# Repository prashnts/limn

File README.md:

## Limn: Pen Plotter with Toolchanger

I wanted to build a plotter that could draw in different colors without
manual color swaps. Limn is my attempt to build one using 3D printed and 3D
printer parts. It has a 5-slot toolchanger, auto tool offset calibration,
can plot on A6 and A5 (~90%) paper, and it runs on klipper.

Build logs are on [Hackaday.io](https://hackaday.io/project/205431-limn-pen-plotter-with-toolchanger),
and the printed parts can be found on [Printables](https://www.printables.com/model/1786450-limn-pen-plotter-with-automatic-tool-changer-parti).

Due to physical constraints and geometry, no two tools/pens will land at the same
point on paper for the given coordinate. This implies that they have each a
certain offset relative to an origin. If we assign a reference pen as the origin,
we can calibrate other tools by comparing the tip position (eg. by drawing and measuring).

This calibration can be done both by hand or automatically. There's an RFID tag
on each tool. Automatic offset calibration requires a sensing surface where the
tools can be probed. Limn can use a Resistive Touch Panel or an FSR matrix
to probe the tool's tips and estimate the XYZ offset with about <0.2mm (best: 0.04mm). 

Then I needed software to actually draw things. I first used PrusaSlicer with
an absurd hack: we can translate "retract", "unretract" as signals to move the
pen up or down... and it worked quite well!

There's an experimental "slicer" in `plot/` which will replace the slicer 
gcode generation. It parses the SVG files natively and handles images, gradient,
text well. It's also "vibecoded". It handles images and gradients with dithering
and the pens can be layered. I intend to refine it further, but it does the job
right now.

Lots of things are currently undocumented and unstable. It's a build log with
code, not a kit: expect to fork it and do some debugging. There's a
`CHANGELOG.md` containing the progress.

## What's where

- `klipper/`: Klipper configuration for the toolchanger motion and printer.
- `ext/limn/`: Klipper extension for complex tasks (eg. calibration).
- `plot/`: SVG to G-code ["Slicer"](plot/README.md).
- `limn_cam/`: (experimental) Z ladder, homographies, scan stitching.
- `micropython/`: firmware for the Dock and the bed MCUs.
- `slicer/`: the old PrusaSlicer based setup, retired.
- `GEOMETRY.md`: plotter coordinates, hardware.
- `docs/`: the details below.

## Development

Install Klipper and clone this repository in the home dir. Create following symlinks for plotter config and extension:

```sh
ln -sfn ~/limn/klipper ~/printer_data/config/limn
ln -sfn ~/limn/ext/limn ~/klipper/klippy/extras/limn
```

The extension requires some packages, so does the plot tool. Extension runs in
Klipper's venv and requires `numpy` to be installed. The plot tool needs `uv`.
In practice these config will require hand tuning for your specific device.

Then add the limn config files to your Klipper config:

```ini
[include limn/limn.cfg]
[include limn/leds.cfg]
[include limn/buzzer.cfg]
```

`printer.cfg` is not linked because Klipper's `SAVE_CONFIG` replaces it with a new one, which would break a symlink.

The plot UI runs next to Klipper (or preferably on a different computer). Its
workspace (the job, dropped SVGs, fonts) is `~/limn/plot-data`.

```sh
cd ~/limn && git pull && uv sync
sudo ln -sf ~/limn/limn_web.conf /etc/supervisor/conf.d/limn_web.conf
sudo supervisorctl reread && sudo supervisorctl update
sudo supervisorctl status limn_web      # then http://<pi>:4219
```

Note that there's no authentication yet, but Moonraker's auth will be supported soon.

A camera tool (wifi/wired) can be calibrated in the UI to scan the bed and plot 
over an existing image (not fully tested yet) or they may be stitched with hugin:

`sudo apt install hugin-tools enblend`

Camera scans are kept in RAM (`/dev/shm/limn-captures`, 2 GB at most).

- Run Tests: `uv run python ext/tests/test_*.py`
- Interact/Update MCUs: `uv run python micropython/mcu.py`
- Camera: `uv sync --extra cam`

## Calibrating the pens

A Bed containg a FSR matrix is used to calibrate XYZ offsets of the pens using
these commands:

```
LRT_CALIBRATE              ; with the reference pen in holder 45
LRT_PROBE_TOOL T=41   ; each other pen: its DX DY DZ go onto its tag
```

TODO: Description.
Everything about meshes, the sensor and its quirks is in `docs/calibration.md`.

## More notes

- `docs/calibration.md`: bed meshes, test marks, the FSR sensor and its survey.
- `docs/leds.md`: the LED matrix and dock strip, and what each state means.
- `docs/toolhead.md`: tool holders and tags, hand-docked tools, the toolhead's wiring, the endoscope.
- `docs/cameras.md`: adding a camera to the Scan tab and calibrating it.

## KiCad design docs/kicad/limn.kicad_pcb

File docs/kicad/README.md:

# Limn: the electronics in KiCad

A KiCad 9 project, `limn.kicad_pro`. The root sheet is the overview, with one sheet per role or board:

| Sheet | File | What's on it |
|---|---|---|
| Power | `power.kicad_sch` | The USB-C PD charger, the 12 V (motion, switched) and 9 V triggers. The bucks sit on their boards: LM_Buck0 by the Melzi, MP_Buck0 on the Aux PCB, MP_Buck1 on the hub board |
| Host (Pi 4) | `host.kicad_sch` | The Pi 4, its USB ports (the hub board on USB-A 3), a camera, I2C1 |
| Tool dock | `tool_dock.kicad_sch` | The MCP23017 and the 5 holder switches, the PN532 tag reader, the indockator strip |
| Melzi (motion) | `melzi.kicad_sch` | The Melzi, motors A/B, the X endstop, the EXT header, the OR gate (going), the plot bed's pull-up, LM_Buck0 (LM2596: +7V5_ZK, the motors only) |
| Toolhead | `toolhead.kicad_sch` | A2. The toolchanger as a PCB of its own (refs 50x, `toolhead_board.kicad_pcb`): the coupling (3 screws 5 V/GND/ID, 4 pogo pins D+/D-/GND/ID), the K lock's motor on 4 pogo pins, its key switch, the cell's pads (J501), 10 uF + 100 nF + an LED on +5V_TOOL, the FFC on an FPC-20P breakout (U506). The FFC (20P 0.5 mm, <= 15 cm) to a second breakout on the axis (U507, wired, no PCB): the USB-C cable to the hub board (W501, 5k1 on CC), CAT6 to LIT, the K ribbon to the Melzi. The axis: Z, the Y/Z endstops, the MPU9250, the endoscope, the BLTouch (gone). The FFC pinout and the tool classes in its notes |
| Aux MCU (rpi) | `aux.kicad_sch` | The Aux PCB, next version: a Waveshare RP2040-Zero (Klipper rpi) on the hub's DN4 (data only), MP_Buck0 (9 V to +5V_LED: the Zero, the LEDs, the buzzer), the buzzer, the MPU9250's I2C; the LEDs off the board |
| Calibration bed | `cal_bed.kicad_sch` | The bed's ID resistor, the FSR node (GP0 BED_DATA, GP2 BED_PROBE) and its 4 x 8 sheet with the row loads |
| Plot bed board | `plot_bed_board.kicad_sch` | The board of `limn.kicad_pcb` and what hangs off it (refs 95x, A2). Above: the two-strip cell (4 BF350s, one full bridge; its nets CELL_* on the head side), W951 = CAT6's bridge pairs to the board's rails (so E+/E- stay their own nets on the toolhead PCB), CAT6 through the chain (orange = E, blue = S, white-green = the tool's ID, green = its GND return on J952.6; the browns spare) to the board at the back: one ADS1220, the touch line (Q951, Q952 in series for BED_PROBE), the tool's ID line, LEDs, J957 to the hub board (the hub's DN3: 5 V on RAW, D+/D- on the Pro Micro's pads underneath; GP9 = `TOOL_5V_EN` back; +5V_TOOL_IN for the bed). Below: the bed dock's work, DETECT (GP29), BED_DATA (GP0, half-duplex), BED_PROBE (GP1), two Pololu Mini MOSFET Slide Switches on MP_Buck1 (+5V_TOOL_IN): U956 on GP4 = the bed (BED_PWR, F952), U957 on GP5 = +5V_SW on J959 (the LEDs, spare), J958, and the dock's pogo J701. Its board headers are 1x1s (J952.1, J957.4, ...), one per pin, to place each where its wiring wants |
| Hub board (USB + tool 5 V) | `hub.kicad_sch` | The FE1.1s hub on its own cable from the Pi (Adafruit USB-C breakout; the Pi powers the hub): DN1 the Melzi, DN2 the tool, DN4 the Aux MCU: data only; DN3 the plot bed board, with the hub's 5 V. The tool's 5 V: 9 V in, MP_Buck1, the Pololu switch, a polyfuse, the tool's USB-C cable on a second Adafruit breakout (U1007: +5V_TOOL, DN2) |
| Beam bed (XY) | `beam_bed.kicad_sch` | A detachable bed (refs 85x), its own PCB (`beam_bed_board.kicad_pcb`): a Waveshare RP2040-Tiny, two 940 nm IR LEDs (AO3400, 100R, pulsed from BED_PWR) and two PT1206BS (10k emitter loads into GP26/27) in an L of 15 mm slots; GP0 = BED_DATA (half-duplex UART, one wire), GP1 = BED_PROBE (the trigger, high = OK), DETECT = the ID resistor only. 0805 resistors. Z from the head's load cell |

How to read it:
- **Sheets meet through global labels** (`USB_*`, `I2C1_*`, `MOT_*`, `ENDSTOP_*`, `PROBE_*`, `BED_*`, ...) and **named power rails** (`+12V`, `+7V5_ZK`, `+9V`, `+5V_LED`, `+5V_TOOL`, `+5V_TOOL_IN`, `+5V_HUB`, `+5V_MELZI`, `+3V3_PI`, `+3V3_AUX`, `+3V3_PB`, `+3V3_PH`). All GND is one net.
- **Solid boxes**: one board or assembly. **Dashed boxes**: planned, or going; their parts are DNP.
- **Boards are blocks** with the pins Limn uses, named as the code names them. The Pro Micro is drawn with its full header in physical order. A USB link is one pin (the cable).
- **References per sheet**: power 1xx, host 2xx, tool dock 3xx, Melzi 4xx, toolhead 5xx, Aux 6xx, the dock's pogo 7xx (J701), calibration bed 8xx (the beam bed 85x), plot bed board 95x, hub board 10xx.
- **Set aside** (2026-10-23, not drawn): the bed on three load-cell feet (the old *Plot bed* sheet, refs 90x), the RTP node, a toolhead MCU, the QRE1113 on the toolhead (U954, R961, C957, GP28). Their drawing code is in `kicad_gen/aside.py`, to bring one back as it was.
- Wires turn at 45°.

Gathered from the code and the docs on 2026-10-16: `notebooks/pinout.md`, `micropython/nodes/*.json`, `klipper/*.cfg`, `projects/limn/content/electronics.md`, `docs/block-diagrams.md`, `docs/load-cell.md`, `TODO.md`.

## Regenerating

```
python3 docs/kicad/gen.py --force --check
```

`kicad_gen/` holds the drawing code: `core.py` (the writer, wires, labels, enclosures), `boards.py` (the blocks), `sheets_a.py` / `sheets_b.py` (one function per sheet), `aside.py` (what is set aside). `gen.py` keeps KiCad's settings in `limn.kicad_pro` and only rewrites its sheet list. `--check` runs ERC, `audit.py` (a net joining two signal pins of one part: the shorts ERC can't see between passive pins) and writes one SVG per sheet into `svg/`. Today (2026-10-23): ERC 0 errors 0 warnings, audit ok. R958 fitted (as traced on the PCB), TOUCH_GP on GP2 only.

Footprints: *Plot bed board* has them (perfboard: R and C in 0805 since 2026-10-23, the fuse in 1812; the modules in `limn.pretty`, written by `kicad_gen/footprints.py`, listed in `fp-lib-table`), and so do the three boards of their own below. The other sheets don't yet.

**One PCB per board.** `limn.kicad_pcb` is the plot bed board's (Update PCB from Schematic, F8). Its perfboard's copper is drawn on Dwgs.User between the hole dots (`perfboard.strips`, 2026-10-23): the top and bottom rows one strip each, the 15 rows between joined down each column in 5 groups of 3. The hub board, the Aux PCB and the beam bed are boards of their own; their parts are "not on board" in the schematic (`sheets_b.own_board`), so F8 never puts them on `limn.kicad_pcb`. Their boards are made from the netlist by `tools/mkboard.py hub|aux|beam|head`: the sheet's parts with a footprint, their nets, a first placement (not routed). It never writes over an existing board (`--force` does); open them in the PCB editor on their own (no project of their own, so no F8: a schematic change goes in by hand or a sync like `tools/sync.py`).

| Board | File | What |
|---|---|---|
| Hub board | `hub_board.kicad_pcb` | Perfboard 38 x 17 holes (as the plot bed board's; its strips not drawn yet). The FE1.1s and the USB-C breakout's pad maps are placeholders: map the real boards before soldering |
| Aux PCB | `aux_board.kicad_pcb` | Perfboard 38 x 17. MP_Buck0 drawn as the same mini buck as MP_Buck1; the LEDs (U602/U603) off the board |
| Toolhead PCB | `toolhead_board.kicad_pcb` | Its own project (`toolhead_board.kicad_pro`): the Toolhead sheet drawn again as `toolhead_board.kicad_sch` (gen.py `STANDALONE`), so the board and the schematic link (F8, cross-probing); its global labels dangle there (their other ends are in `limn.kicad_pro`). Edit the generator, not one copy. A PCB, 61 x 50.8 mm for now (a first outline: shape it to the head). The FPC-20P breakout (`limn:FPC20_breakout`, from its photo; its STEP to come), SMD pogo pins D 2.0 x 5 (`limn:Pogo_pin_D2.0_L5.0`), the K motor with its flex on 4 pogos (`limn:Stepper_slider_5mm_flex4`), the key switch (`limn:Micro_limit_sw_inline`), M3 pad holes for the screws, the cell's wires (SolderWire 1x04), 0805. STEPs from the user's models in `limn.3dshapes/` |
| Beam bed | `beam_bed_board.kicad_pcb` | A PCB, 43.2 x 33.0 mm, 1.6 mm (thinner for the bed: set it in Board Setup). 0805, the LEDs/PTs in 1206 (where they go depends on the slots), the pogo as a 1x05 2.54 mm row |

The RP2040-Zero and RP2040-Tiny (same 23 castellated holes, rows 15.24 mm apart) use Waveshare's pin numbers (GP0-15 = 1-16, GP26-29 = 17-20, 3V3 21, GND 22, 5V 23; 24 = the USB), with Waveshare's STEP models in `limn.3dshapes/` (gzipped, `.stpZ`). The library footprints point at KiCad's 3D models (`${KICAD9_3DMODEL_DIR}`): install `kicad-packages3d` to see them.

Once the schematic is edited in KiCad, regenerating overwrites the edits: don't, or move the change into the generator first.

## To fill in

- [ ] The FE1.1s breakout (which board) and its pad map: `limn:FE1.1s_USB_hub_breakout` is a placeholder (U1002).
- [ ] The Adafruit USB-C breakout's pin order (U1001: VBUS, D+, D-, GND in a row for now).
- [ ] The beam bed's pogo: its pitch and pin order (J851: a 1x05 2.54 mm row for now); where the LEDs/PTs sit against the slots; the board's thickness.
- [ ] The toolhead PCB: the K flex pads' pitch and place (3.0 mm past the motor's end, a placeholder), the key switch's tabs (from the model), the screws' size and places, the outline; the breakout's STEP (the user, 2026-10-30).
- [x] The FFC: 1 -> 1 (the cell reads right through pins 2-5, 2026-11-01; reversed they'd land on 16-19). Meter 13-15 before power anyway.
- [ ] The bed pogo connector's pin order (power, GND, DETECT, TX, RX).
- [ ] The cameras on the Pi: which is on which port, and which devices are on the hub vs straight on the Pi today.
- [ ] The buzzer circuit: gate resistor, supply, flyback diode.
- [ ] The Pico's VSYS (USB only, or the Aux PCB's LM2596 through a diode?), and where the MPU9250 gets its VCC.
- [ ] The MCP23017 breakout's RST pin.
- [x] The ADS1220 module's header order: from the photo (2026-10-18), DIP numbering, top view; footprint `limn:ADS1220_module`.
- [ ] The Pololu Mini MOSFET Slide Switch's pad map (U1006 on the hub board).
- [ ] Where the Pro Micro's D+/D- pads are underneath (footprint pads 30/31 are placeholders by the USB-C).
- [ ] `klipper/leds.cfg` for the RP2040-Zero (lamp gpio16 → 14, indockator gpio17 → 13) and the merged Dock/plot bed firmware (dock pins GP29, GP0/1, GP4 = BED_EN, GP5 = SW_5V_EN, high = on; CS2 on GP21, LED_R/LED_G gone).
- [ ] The FSR board's series resistors on the rows (values).
- [ ] The Melzi's endstop headers (2 or 3 pins), and whether the BLTouch and the OR gate are already out.

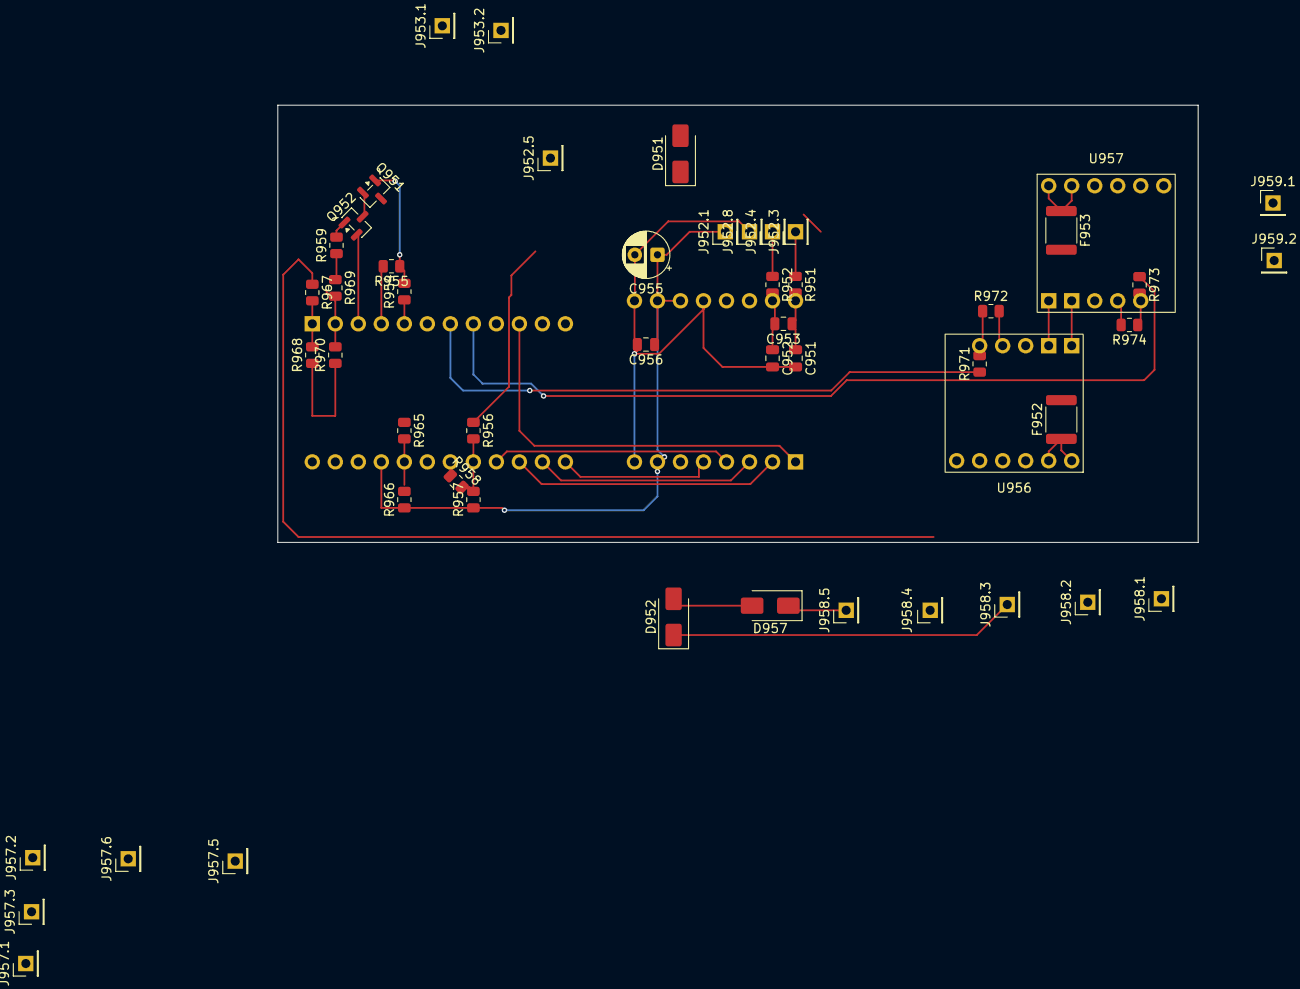
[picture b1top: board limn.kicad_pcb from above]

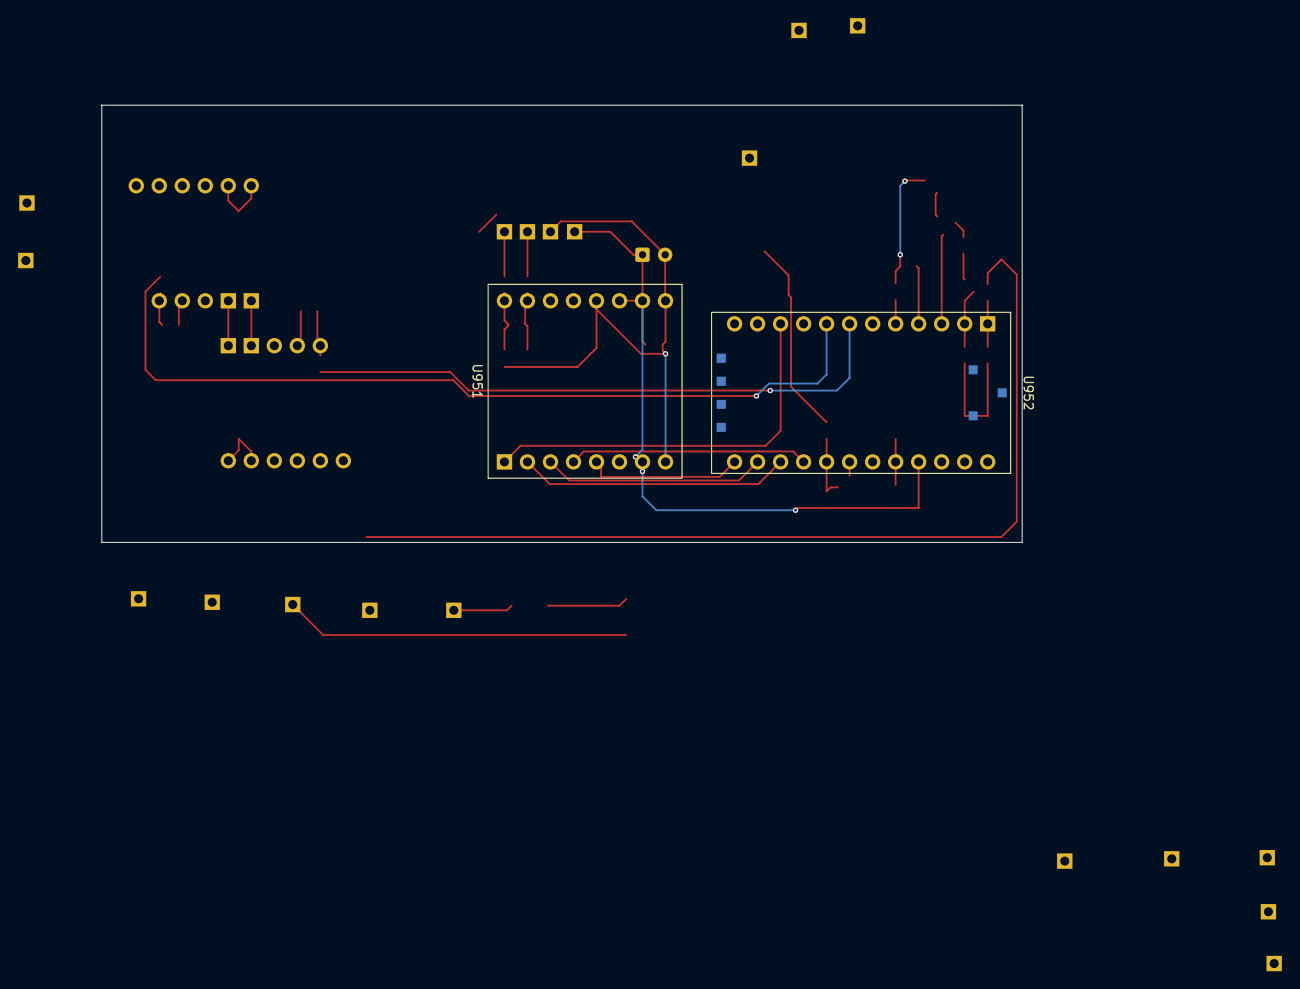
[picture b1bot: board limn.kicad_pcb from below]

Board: 2 copper layers, 101.6 x 48.3 mm, 53 parts (2 on the bottom side), 37 nets.

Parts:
C951, C952: 4n7 C0G; C_0805_2012Metric
C953: 47n; C_0805_2012Metric
C955: 47u; CP_Radial_D5.0mm_P2.50mm
C956: 100n; C_0805_2012Metric
D951, D952, D957: SMAJ3.3A; D_SMA
F952, F953: PPTC 1812 1A 6V; Fuse_1812_4532Metric
J952.1: CAT6 1; PinHeader_1x01_P2.54mm_Vertical
J952.3: CAT6 3; PinHeader_1x01_P2.54mm_Vertical
J952.4: CAT6 4; PinHeader_1x01_P2.54mm_Vertical
J952.5: CAT6 5; PinHeader_1x01_P2.54mm_Vertical
J952.8: CAT6 8; PinHeader_1x01_P2.54mm_Vertical
J953.1: to the Melzi (EXT A4) 1; PinHeader_1x01_P2.54mm_Vertical
J953.2: to the Melzi (EXT A4) 2; PinHeader_1x01_P2.54mm_Vertical
J957.1: to the hub board (J1002) 1; PinHeader_1x01_P2.54mm_Vertical
J957.2: to the hub board (J1002) 2; PinHeader_1x01_P2.54mm_Vertical
J957.3: to the hub board (J1002) 3; PinHeader_1x01_P2.54mm_Vertical
J957.5: to the hub board (J1002) 5; PinHeader_1x01_P2.54mm_Vertical
J957.6: to the hub board (J1002) 6; PinHeader_1x01_P2.54mm_Vertical
J958.1: to the bed dock (pogo) 1; PinHeader_1x01_P2.54mm_Vertical
J958.2: to the bed dock (pogo) 2; PinHeader_1x01_P2.54mm_Vertical
J958.3: to the bed dock (pogo) 3; PinHeader_1x01_P2.54mm_Vertical
J958.4: to the bed dock (pogo) 4; PinHeader_1x01_P2.54mm_Vertical
J958.5: to the bed dock (pogo) 5; PinHeader_1x01_P2.54mm_Vertical
J959.1: +5V Toolchanger USB 1; PinHeader_1x01_P2.54mm_Vertical
J959.2: +5V Toolchanger USB 2; PinHeader_1x01_P2.54mm_Vertical
Q951: MMBT3904 / BC847 (SOT-23); SOT-23
Q952: AO3400; SOT-23
R951, R952, R958, R959, R971, R973: 1k; R_0805_2012Metric
R954, R968: 4k7; R_0805_2012Metric
R955, R972, R974: 100k; R_0805_2012Metric
R956, R965, R967, R969: 100R; R_0805_2012Metric
R957, R966, R970: 10k; R_0805_2012Metric
U951: ADS1220 module (the sum chip); ADS1220_module
U952: SparkFun Pro Micro RP2040 (top view, USB-C up); SparkFun_Pro_Micro_RP2040
U956, U957: Pololu mini slide sw. #2810; Pololu_Mini_MOSFET_Slide_Switch

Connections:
+3V3_PH: C955.1, C956.1, J952.1.1, R957.1, R966.1, R968.1, R970.1, U951.7 (DVDD), U951.10 (AVDD), U951.11 (REFP0), U952.16 (3V3)
+5V_HUB: J957.1.1, U952.13 (RAW)
+5V_SW: F953.2, J959.1.1
+5V_TOOL_IN: J957.5.1, U956.1 (VIN), U957.1 (VIN)
/Plot bed board/AIN_N: C952.1, C953.2, R952.2, U951.15 (AIN1)
/Plot bed board/AIN_P: C951.1, C953.1, R951.2, U951.16 (AIN0)
/Plot bed board/CIPO: U951.2 (MISO), U952.22 (GP20/CIPO)
/Plot bed board/COPI: U951.3 (MOSI), U952.23 (GP23/COPI)
/Plot bed board/CS2: U951.5 (CS), U952.24 (GP21/CS)
/Plot bed board/DRDY2: U951.1 (DRDY), U952.10 (GP7)
/Plot bed board/ID_PU: R958.1, U952.19 (GP27/A1)
/Plot bed board/SCK: U951.4 (SCLK), U952.21 (GP22/SCK)
/Plot bed board/SIG_N: J952.4.1, R952.1
/Plot bed board/SIG_P: J952.3.1, R951.1
/Plot bed board/TOOL_ID_IN: R956.2, R957.2, R958.2, U952.20 (GP26/A0)
/Plot bed board/TOUCH_GP: R954.1, U952.5 (GP2)
BED_DATA: J958.4.1, R967.1
BED_DETECT: D952.1 (A1), J958.3.1, R965.1
BED_DET_IN: R965.2, R966.2, U952.17 (GP29/A3)
BED_EN: R971.1, U952.7 (GP4)
BED_IO: R967.2, R968.2, U952.1 (GP0/TX)
BED_PROBE: D957.1 (A1), J958.5.1, R959.1, R969.1
BED_PROBE_IN: R969.2, R970.2, U952.2 (GP1/RX)
BED_PWR: F952.2, J958.1.1
GND: C951.2, C952.2, C955.2, C956.2, D951.2 (A2), D952.2 (A2), D957.2 (A2), J952.8.1, J953.2.1, J957.6.1, J958.2.1, J959.2.1, Q952.2 (S), R955.2, R972.2, R974.2, U951.8 (DGND), U951.9 (AGND), U951.12 (REFN0), U952.3 (GND), U952.4 (GND), U952.14 (GND), U956.3 (GND), U957.3 (GND)
unnamed: Q951.1 (B), R954.2, R955.1
unnamed: Q951.2 (E), Q952.3 (D)
unnamed: Q952.1 (G), R959.2
unnamed: R971.2, R972.1, U956.2 (ON)
unnamed: F952.1, U956.4 (VOUT)
unnamed: R973.2, R974.1, U957.2 (ON)
unnamed: F953.1, U957.4 (VOUT)
PM_USB_DN: J957.3.1, U952.31 (D-)
PM_USB_DP: J957.2.1, U952.30 (D+)
PROBE_A4: J953.1.1, Q951.3 (C)
SW_5V_EN: R973.1, U952.8 (GP5)
TOOL_ID: D951.1 (A1), J952.5.1, R956.1

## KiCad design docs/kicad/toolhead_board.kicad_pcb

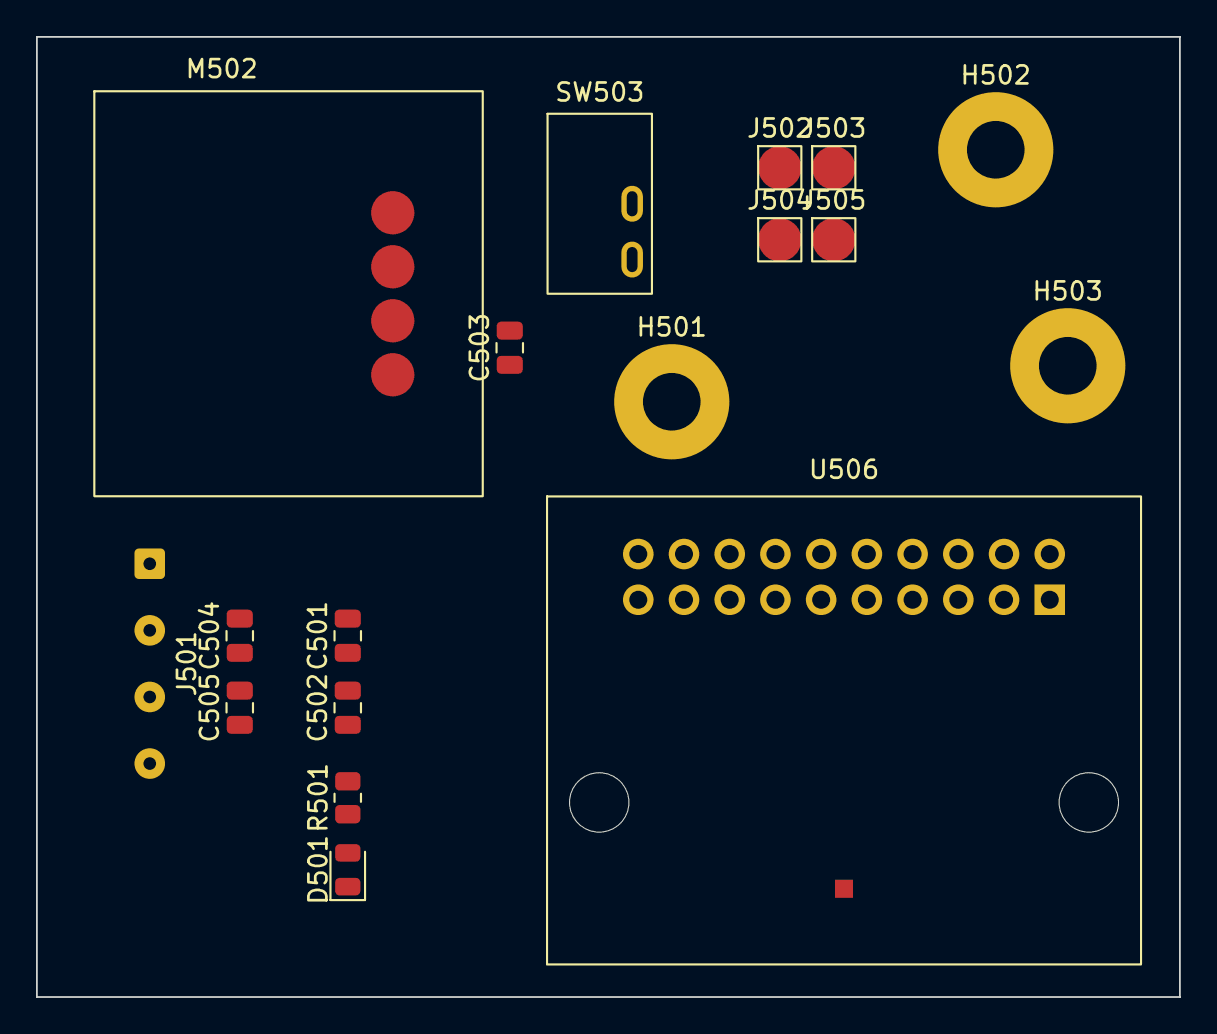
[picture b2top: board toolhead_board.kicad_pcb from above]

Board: 2 copper layers, 63.5 x 53.3 mm, 18 parts (0 on the bottom side), 15 nets, no tracks yet.

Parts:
C501: 10u; C_0805_2012Metric
C502, C505: 100n; C_0805_2012Metric
C503: 10n; C_0805_2012Metric
C504: 10n C0G; C_0805_2012Metric
D501: LED yellow; LED_0805_2012Metric
H501: screw right, 5V; MountingHole_3.2mm_M3_Pad
H502: screw left, GND; MountingHole_3.2mm_M3_Pad
H503: screw top, ID; MountingHole_3.2mm_M3_Pad
J501: cell pads; SolderWire-0.127sqmm_1x04_P3.7mm_D0.48mm_OD1mm
J502, J503, J504, J505: pogo; Pogo_pin_D2.0_L5.0
M502: 10 mm linear micro stepper (K, the key lock); Stepper_slider_5mm_flex4
R501: 4k7; R_0805_2012Metric
SW503: key switch (K); Micro_limit_sw_inline
U506: FPC-20P breakout (head); FPC20_breakout

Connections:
+5V_TOOL: C501.1, C502.1, H501.1, R501.1, U506.13, U506.14, U506.15
CELL_EXC_N: C505.2, J501.4, U506.5
CELL_EXC_P: C505.1, J501.1, U506.2
CELL_SIG_N: C504.2, J501.3, U506.4
CELL_SIG_P: C504.1, J501.2, U506.3
ENDSTOP_K: C503.1, SW503.1, U506.7
GND: C501.2, C502.2, C503.2, D501.1, H502.1, J504.1, SW503.2, U506.1, U506.6, U506.8, U506.11, U506.16
MOT_K_1A: M502.1, U506.17
MOT_K_1B: M502.2, U506.18
MOT_K_2A: M502.3, U506.19
MOT_K_2B: M502.4, U506.20
unnamed: D501.2, R501.2
TOOL_ID: H503.1, J505.1, U506.12
TOOL_USB_DN: J503.1, U506.10
TOOL_USB_DP: J502.1, U506.9

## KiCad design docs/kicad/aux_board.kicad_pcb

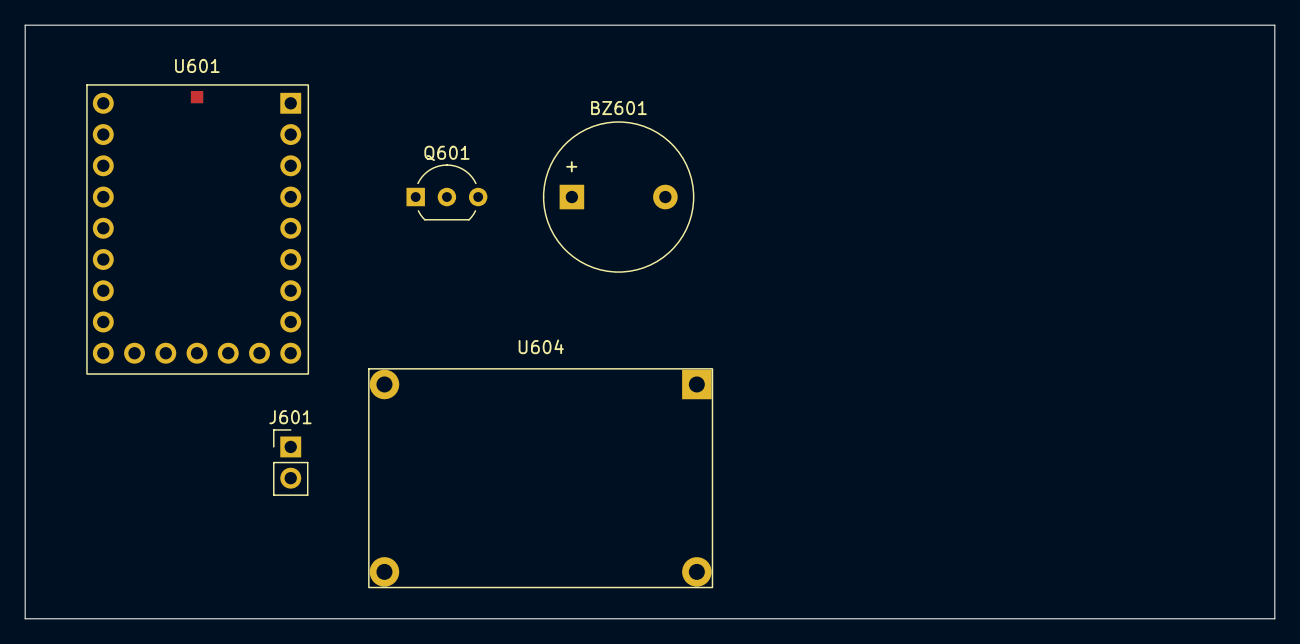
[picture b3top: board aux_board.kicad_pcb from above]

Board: 2 copper layers, 101.6 x 48.3 mm, 5 parts (0 on the bottom side), 5 nets, no tracks yet.

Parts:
BZ601: buzzer; Buzzer_12x9.5RM7.6
J601: 9 V in (Trigger1); PinHeader_1x02_P2.54mm_Vertical
Q601: 2N7000; TO-92_Inline_Wide
U601: RP2040-Zero (rpi); Waveshare_RP2040_Zero
U604: MP1495 5 V (MP_Buck0); Mini_buck_3A

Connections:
+5V_LED: BZ601.1, U601.23, U604.3
+9V: J601.1, U604.1
GND: J601.2, Q601.1, U601.22, U604.2, U604.4
unnamed: BZ601.2, Q601.3
unnamed: Q601.2, U601.10

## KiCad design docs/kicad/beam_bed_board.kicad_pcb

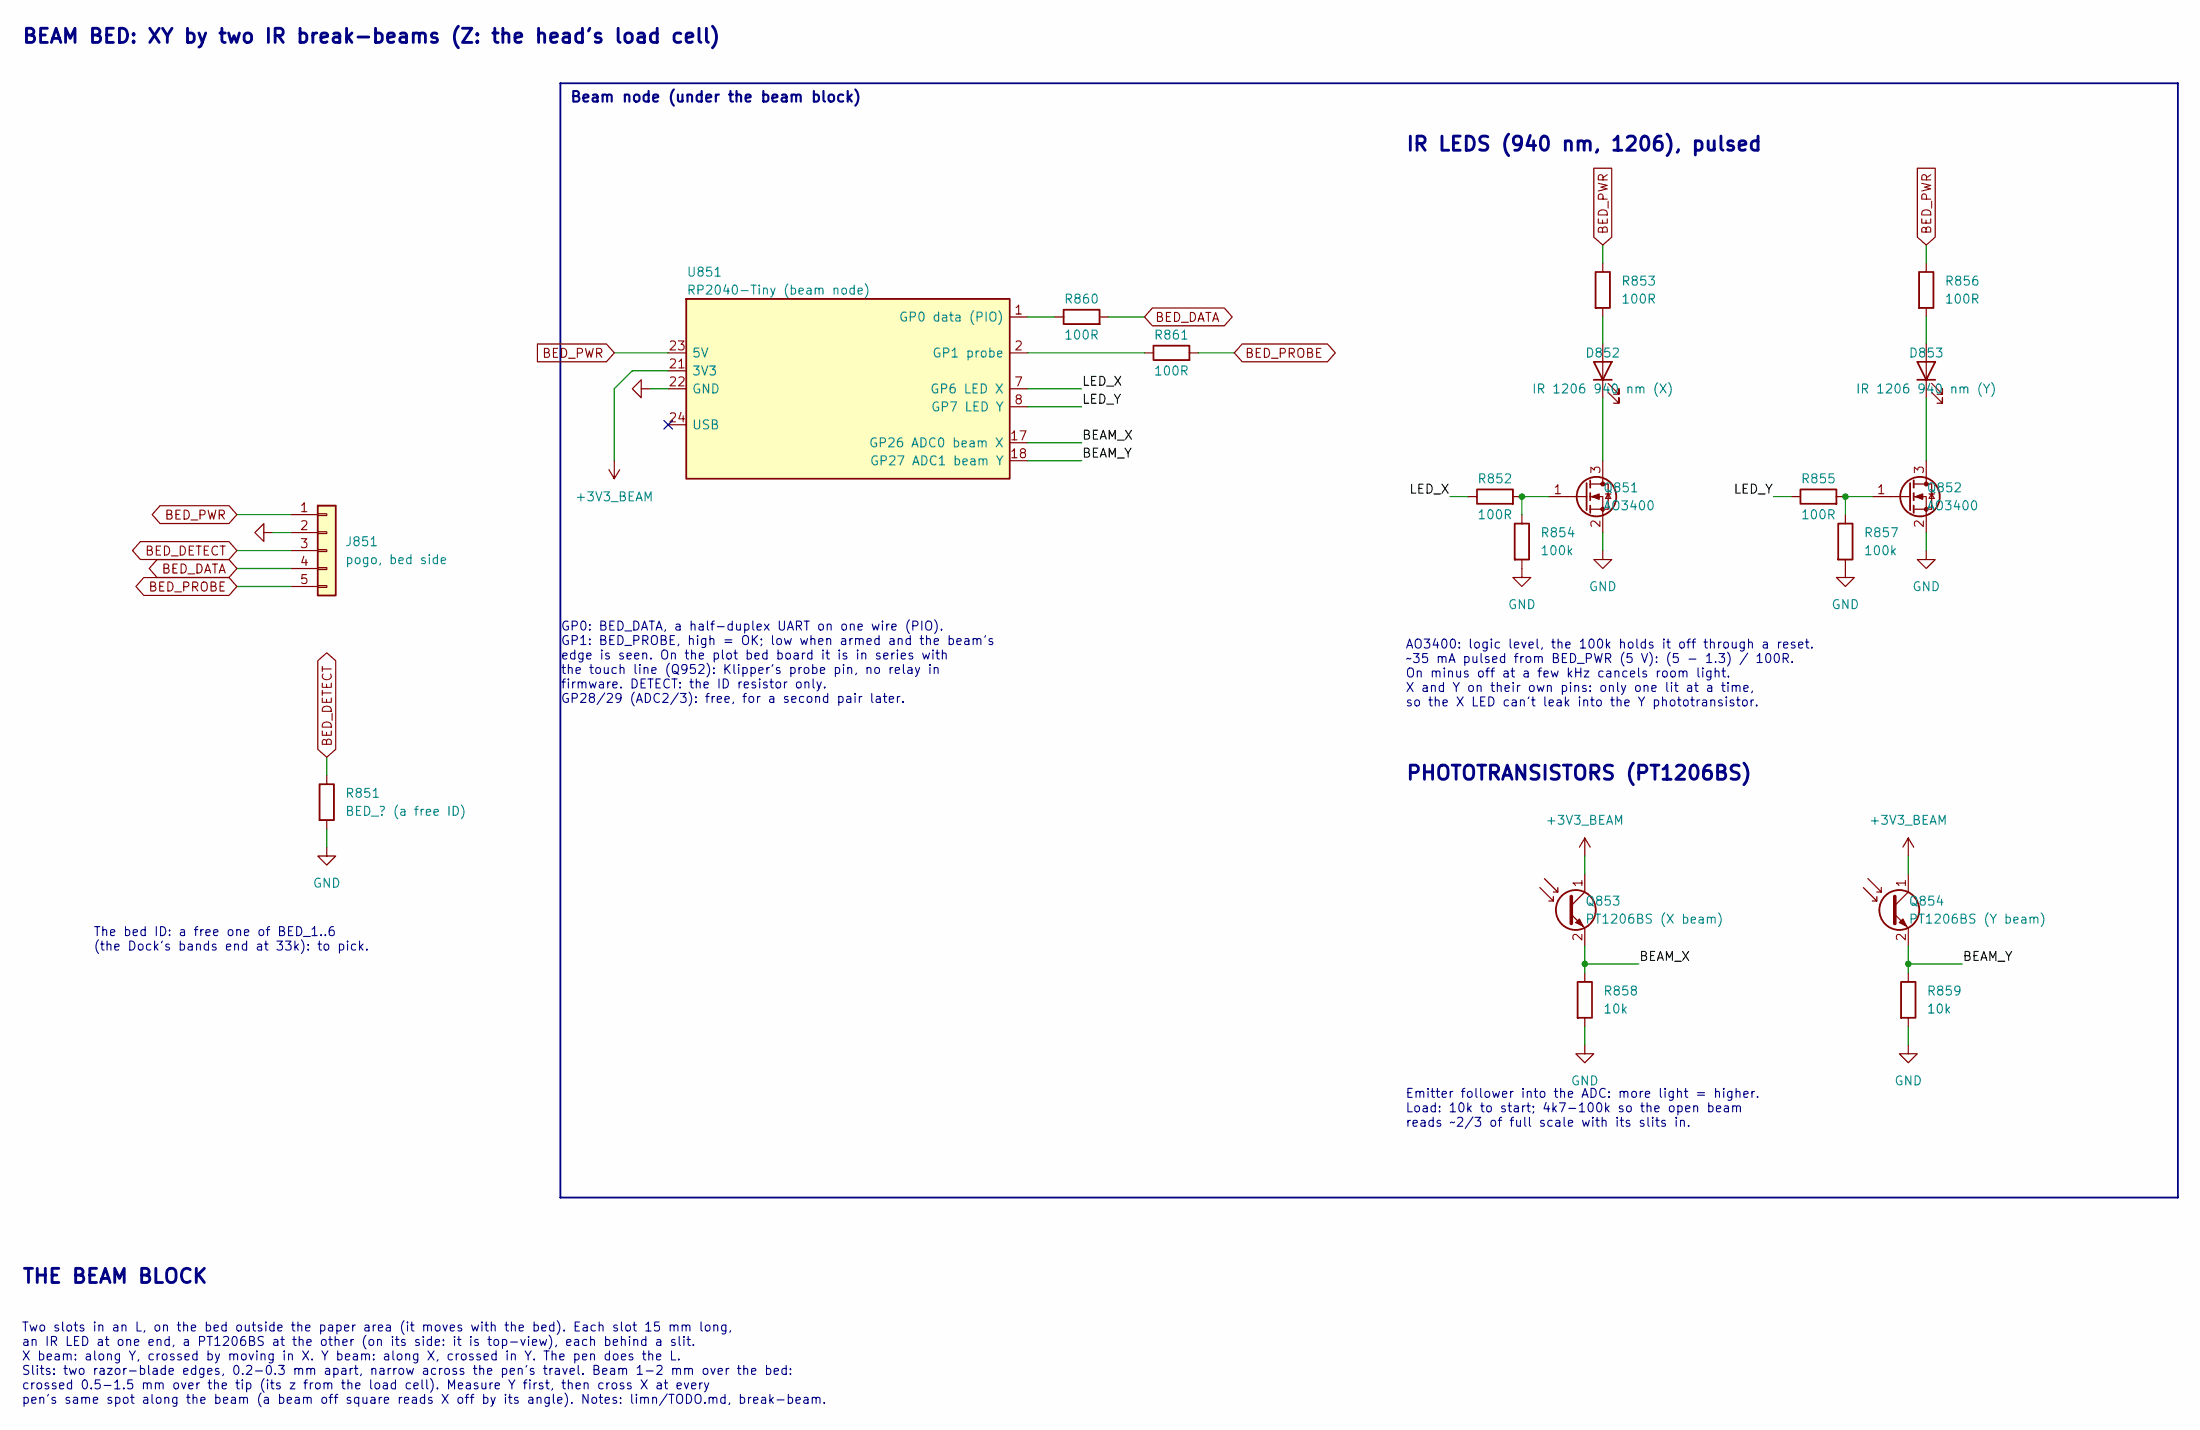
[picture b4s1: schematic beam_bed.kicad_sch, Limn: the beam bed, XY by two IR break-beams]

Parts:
D852: IR 1206 940 nm (X); LED_1206_3216Metric
D853: IR 1206 940 nm (Y); LED_1206_3216Metric
J851: pogo, bed side; PinHeader_1x05_P2.54mm_Vertical
Q851, Q852: AO3400; SOT-23
Q853: PT1206BS (X beam); LED_1206_3216Metric
Q854: PT1206BS (Y beam); LED_1206_3216Metric
R851: BED_? (a free ID); R_0805_2012Metric
R852, R853, R855, R856, R860, R861: 100R; R_0805_2012Metric
R854, R857: 100k; R_0805_2012Metric
R858, R859: 10k; R_0805_2012Metric
U851: RP2040-Tiny (beam node); Waveshare_RP2040_Tiny

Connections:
+3V3_BEAM: Q853.1 (C), Q854.1 (C), U851.21 (3V3)
/Beam bed (XY)/BEAM_X: Q853.2 (E), R858.1, U851.17 (GP26 ADC0 beam X)
/Beam bed (XY)/BEAM_Y: Q854.2 (E), R859.1, U851.18 (GP27 ADC1 beam Y)
/Beam bed (XY)/LED_X: R852.1, U851.7 (GP6 LED X)
/Beam bed (XY)/LED_Y: R855.1, U851.8 (GP7 LED Y)
BED_DATA: J851.4, R860.2
BED_DETECT: J851.3, R851.1
BED_PROBE: J851.5, R861.2
BED_PWR: J851.1, R853.1, R856.1, U851.23 (5V)
GND: J851.2, Q851.2 (S), Q852.2 (S), R851.2, R854.2, R857.2, R858.2, R859.2, U851.22 (GND)
unnamed: D852.2 (A), R853.2
unnamed: D852.1 (K), Q851.3 (D)
unnamed: D853.2 (A), R856.2
unnamed: D853.1 (K), Q852.3 (D)
unnamed: Q851.1 (G), R852.2, R854.1
unnamed: Q852.1 (G), R855.2, R857.1
unnamed: R860.1, U851.1 (GP0 data (PIO))
unnamed: R861.1, U851.2 (GP1 probe)

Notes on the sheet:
BEAM BED: XY by two IR break-beams (Z: the head's load cell)
The bed ID: a free one of BED_1..6 (the Dock's bands end at 33k): to pick.
GP0: BED_DATA, a half-duplex UART on one wire (PIO). GP1: BED_PROBE, high = OK; low when armed and the beam's edge is seen. On the plot bed board it is in series with the touch line (Q952): Klipper's probe pin, no relay in firmware. DETECT: the ID resistor only. GP28/29 (ADC2/3): free, for a second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
IR LEDS (940 nm, 1206), pulsed
AO3400: logic level, the 100k holds it off through a reset. ~35 mA pulsed from BED_PWR (5 V): (5 - 1.3) / 100R. On minus off at a few kHz cancels room light. X and Y on their own pins: only one lit at a time, so the X LED can't leak into the Y phototransistor.
PHOTOTRANSISTORS (PT1206BS)
Emitter follower into the ADC: more light = higher. Load: 10k to start; 4k7-100k so the open beam reads ~2/3 of full scale with its slits in.
Beam node (under the beam block)
THE BEAM BLOCK
Two slots in an L, on the bed outside the paper area (it moves with the bed). Each slot 15 mm long, an IR LED at one end, a PT1206BS at the other (on its side: it is top-view), each behind a slit. X beam: along Y, crossed by moving in X. Y beam: along X, crossed in Y. The pen does the L. Slits: two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

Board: 2 copper layers, 19 parts (0 on the bottom side), 18 nets, no tracks yet.

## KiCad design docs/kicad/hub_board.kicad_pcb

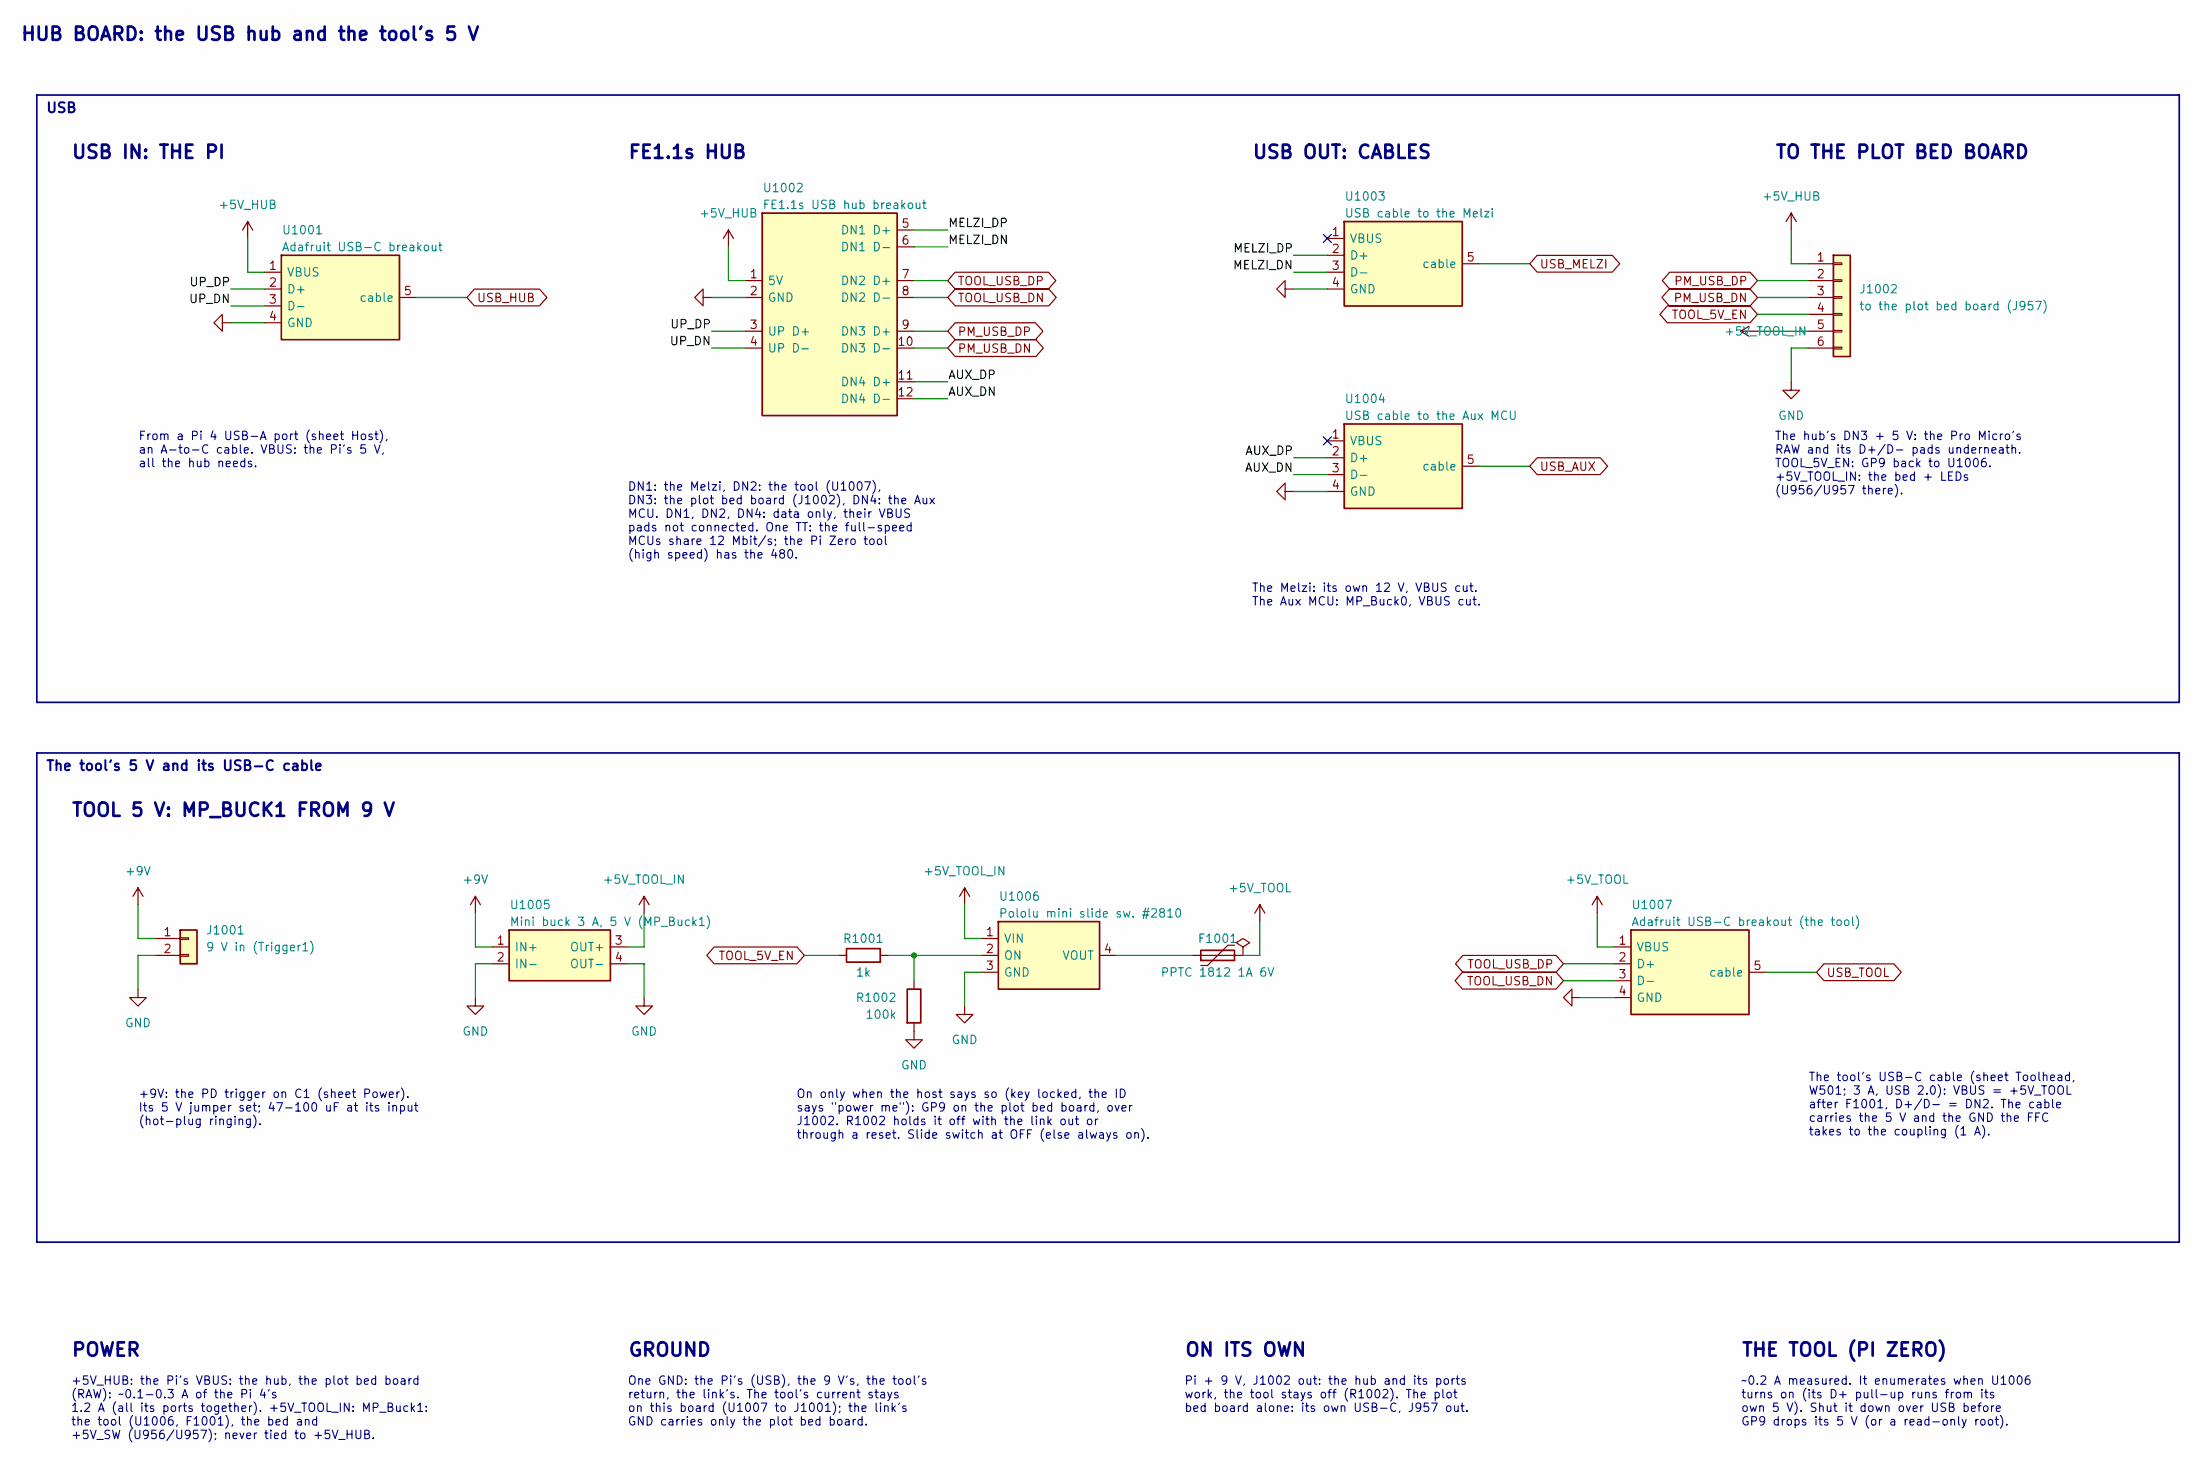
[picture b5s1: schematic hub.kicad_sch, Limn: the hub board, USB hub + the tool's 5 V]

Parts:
F1001: PPTC 1812 1A 6V; Fuse_1812_4532Metric
J1001: 9 V in (Trigger1); PinHeader_1x02_P2.54mm_Vertical
J1002: to the plot bed board (J957); PinHeader_1x06_P2.54mm_Vertical
R1001: 1k; R_0805_2012Metric
R1002: 100k; R_0805_2012Metric
U1001: Adafruit USB-C breakout; Adafruit_USB_C_breakout
U1002: FE1.1s USB hub breakout; FE1.1s_USB_hub_breakout
U1003: USB cable to the Melzi; USB_cable_pads
U1004: USB cable to the Aux MCU; USB_cable_pads
U1005: Mini buck 3 A, 5 V (MP_Buck1); Mini_buck_3A
U1006: Pololu mini slide sw. #2810; Pololu_Mini_MOSFET_Slide_Switch
U1007: Adafruit USB-C breakout (the tool); Adafruit_USB_C_breakout

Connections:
+5V_HUB: J1002.1, U1001.1 (VBUS), U1002.1 (5V)
+5V_TOOL: F1001.2, U1007.1 (VBUS); also elsewhere on the board
+5V_TOOL_IN: J1002.5, U1005.3 (OUT+), U1006.1 (VIN)
+9V: J1001.1, U1005.1 (IN+)
/Hub board (USB + tool 5 V)/AUX_DN: U1002.12 (DN4 D-), U1004.3 (D-)
/Hub board (USB + tool 5 V)/AUX_DP: U1002.11 (DN4 D+), U1004.2 (D+)
/Hub board (USB + tool 5 V)/MELZI_DN: U1002.6 (DN1 D-), U1003.3 (D-)
/Hub board (USB + tool 5 V)/MELZI_DP: U1002.5 (DN1 D+), U1003.2 (D+)
/Hub board (USB + tool 5 V)/UP_DN: U1001.3 (D-), U1002.4 (UP D-)
/Hub board (USB + tool 5 V)/UP_DP: U1001.2 (D+), U1002.3 (UP D+)
GND: J1001.2, J1002.6, R1002.2, U1001.4 (GND), U1002.2 (GND), U1003.4 (GND), U1004.4 (GND), U1005.2 (IN-), U1005.4 (OUT-), U1006.3 (GND), U1007.4 (GND); also elsewhere on the board
unnamed: R1001.2, R1002.1, U1006.2 (ON)
unnamed: F1001.1, U1006.4 (VOUT)
PM_USB_DN: J1002.3, U1002.10 (DN3 D-)
PM_USB_DP: J1002.2, U1002.9 (DN3 D+)
TOOL_5V_EN: J1002.4, R1001.1
TOOL_USB_DN: U1002.8 (DN2 D-), U1007.3 (D-); also elsewhere on the board
TOOL_USB_DP: U1002.7 (DN2 D+), U1007.2 (D+); also elsewhere on the board
USB_AUX: U1004.5 (cable)
USB_HUB: U1001.5 (cable)
USB_MELZI: U1003.5 (cable)

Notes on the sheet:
HUB BOARD: the USB hub and the tool's 5 V
USB IN: THE PI
From a Pi 4 USB-A port (sheet Host), an A-to-C cable. VBUS: the Pi's 5 V, all the hub needs.
FE1.1s HUB
DN1: the Melzi, DN2: the tool (U1007), DN3: the plot bed board (J1002), DN4: the Aux MCU. DN1, DN2, DN4: data only, their VBUS pads not connected. One TT: the full-speed MCUs share 12 Mbit/s; the Pi Zero tool (high speed) has the 480.
USB OUT: CABLES
The Melzi: its own 12 V, VBUS cut. The Aux MCU: MP_Buck0, VBUS cut.
TO THE PLOT BED BOARD
The hub's DN3 + 5 V: the Pro Micro's RAW and its D+/D- pads underneath. TOOL_5V_EN: GP9 back to U1006. +5V_TOOL_IN: the bed + LEDs (U956/U957 there).
USB
TOOL 5 V: MP_BUCK1 FROM 9 V
+9V: the PD trigger on C1 (sheet Power). Its 5 V jumper set; 47-100 uF at its input (hot-plug ringing).
On only when the host says so (key locked, the ID says "power me"): GP9 on the plot bed board, over J1002. R1002 holds it off with the link out or through a reset. Slide switch at OFF (else always on).
The tool's USB-C cable (sheet Toolhead, W501; 3 A, USB 2.0): VBUS = +5V_TOOL after F1001, D+/D- = DN2. The cable carries the 5 V and the GND the FFC takes to the coupling (1 A).
The tool's 5 V and its USB-C cable
POWER
+5V_HUB: the Pi's VBUS: the hub, the plot bed board (RAW): ~0.1-0.3 A of the Pi 4's 1.2 A (all its ports together). +5V_TOOL_IN: MP_Buck1: the tool (U1006, F1001), the bed and +5V_SW (U956/U957); never tied to +5V_HUB.
GROUND
One GND: the Pi's (USB), the 9 V's, the tool's return, the link's. The tool's current stays on this board (U1007 to J1001); the link's GND carries only the plot bed board.
ON ITS OWN
Pi + 9 V, J1002 out: the hub and its ports work, the tool stays off (R1002). The plot bed board alone: its own USB-C, J957 out.
THE TOOL (PI ZERO)
~0.2 A measured. It enumerates when U1006 turns on (its D+ pull-up runs from its own 5 V). Shut it down over USB before GP9 drops its 5 V (or a read-only root).

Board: 2 copper layers, 12 parts (0 on the bottom side), 18 nets, no tracks yet.

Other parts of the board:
J1003: CAT6 #2 (to the tool); PinHeader_1x08_P2.54mm_Vertical

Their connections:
+5V_TOOL: J1003.1, J1003.2, J1003.3; also elsewhere on the board
GND: J1003.6, J1003.7, J1003.8; also elsewhere on the board
TOOL_USB_DN: J1003.5; also elsewhere on the board
TOOL_USB_DP: J1003.4; also elsewhere on the board

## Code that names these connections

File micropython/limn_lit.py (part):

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
# GP high = the NPN conducts = the Klipper pin reads low = OK.
touch_out = Pin(NODE['touch_out'], Pin.OUT, value=0)
bed_en = Pin(NODE['bed_en'], Pin.OUT, value=0)
sw_5v = Pin(NODE['sw_5v'], Pin.OUT, value=0)
bed_probe = Pin(NODE['bed_probe'], Pin.IN)      # R970 pulls it up: OK with no bed
bed_detect = ADC(Pin(NODE['bed_detect']))
tool_pu = Pin(NODE['tool_pu'], Pin.IN)          # high only for the tool's link, later
tool_id = ADC(Pin(NODE['tool_id']))
npx = NeoPixel(Pin(NODE.get('led', 25)), 1)
link = from_config(NODE)
if link.down:
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
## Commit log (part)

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2026-05-16 feat: init module for probing
2026-05-25 add upy firmware for the bed + notes
2026-05-26 add upy firmware for the dock
2026-05-27 update extension
2026-06-09 feat: full pen calibration with resistive panel
2026-06-10 feat: apply pen calibration and draw
2026-06-11 feat: implement calibrated plotting
2026-06-13 update slicer conf

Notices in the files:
micropython/limn_lit.py:
Copyright (C) 2026 Prashant Sinha <limn@noop.pw>
This file may be distributed under the terms of the GNU GPLv3 license.
